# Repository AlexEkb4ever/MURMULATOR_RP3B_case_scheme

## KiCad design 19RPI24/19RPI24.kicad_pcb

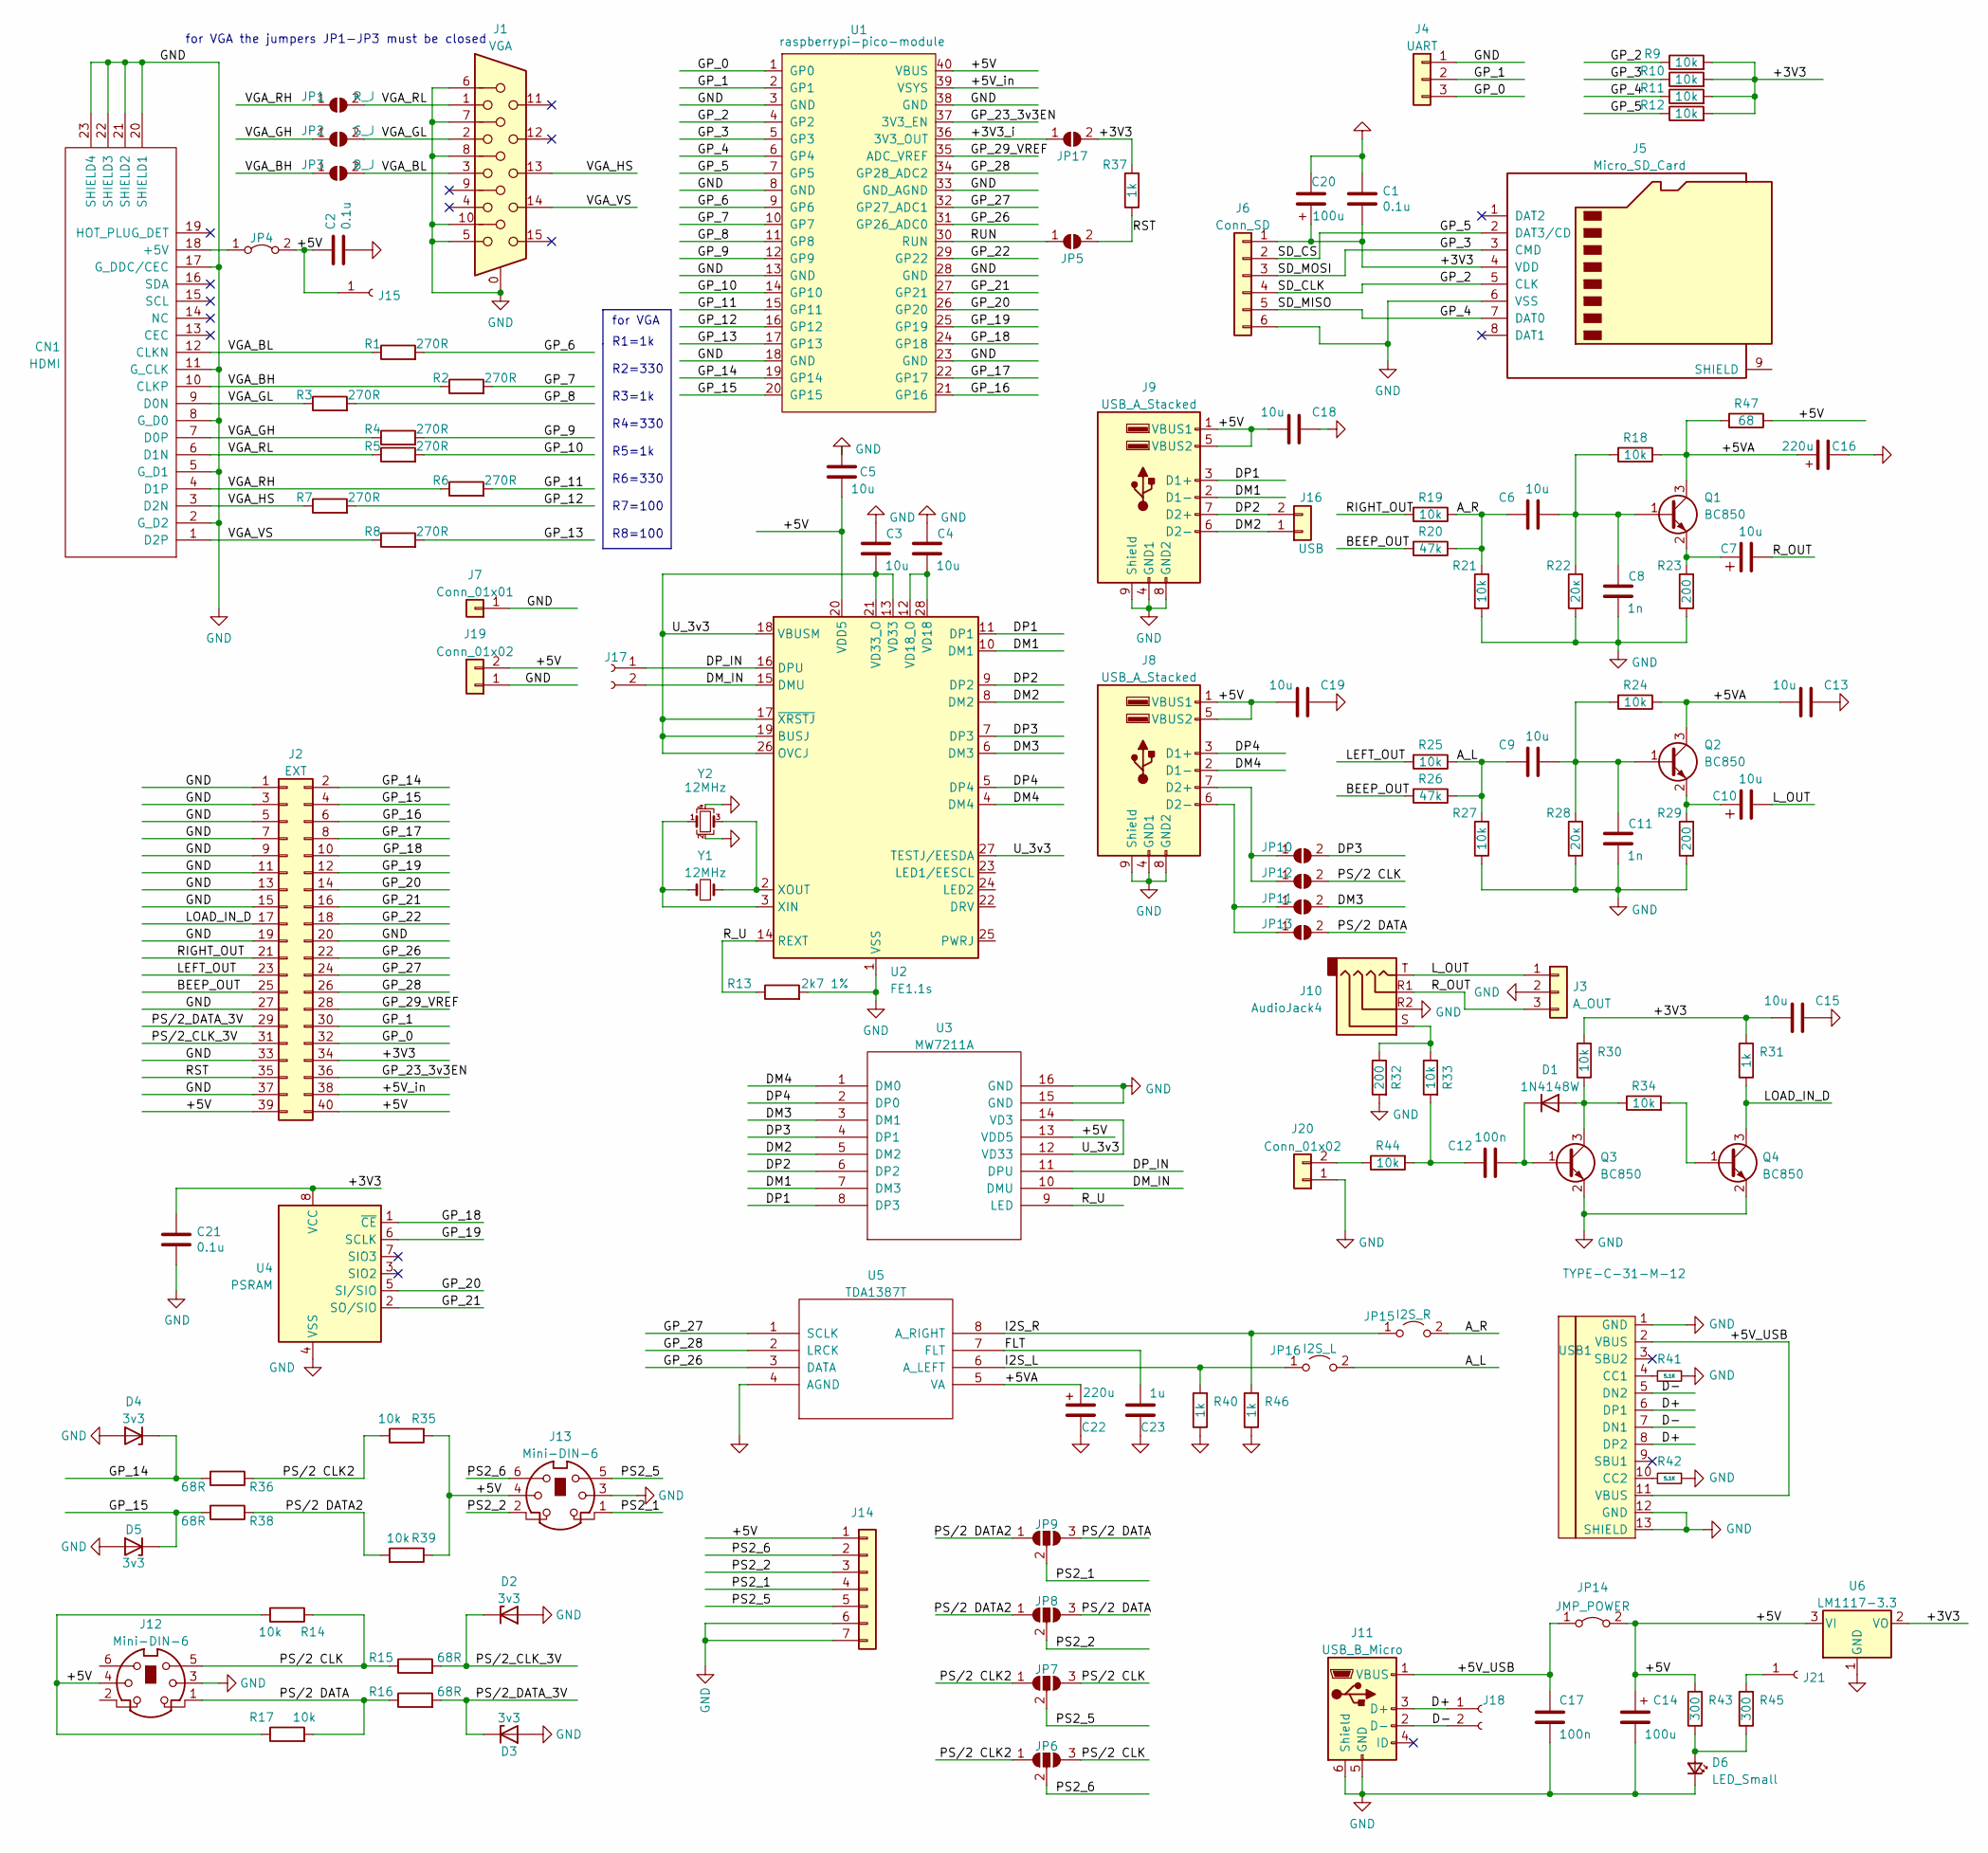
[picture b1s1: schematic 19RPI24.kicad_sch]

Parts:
C1, C21: 0.1u; C_0805_2012Metric_Pad1.18x1.45mm_HandSolder
C2: 0.1u; R_0805_PLUS
C3, C4, C5, C6, C9, C13, C15, C18, C19: 10u; C_0805_2012Metric_Pad1.18x1.45mm_HandSolder
C7, C10: 10u; c_comb_pol
C8, C11: 1n; C_0805_2012Metric_Pad1.18x1.45mm_HandSolder
C12, C17: 100n; C_0805_2012Metric_Pad1.18x1.45mm_HandSolder
C14, C20: 100u; c_comb_pol
C16: 220u; CP_EIA-3528-21_Kemet-B_Pad1.50x2.35mm_HandSolder
C22: 220u; CP_EIA-6032-28_Kemet-C
C23: 1u; C_0805_2012Metric_Pad1.18x1.45mm_HandSolder
CN1: HDMI
D1: 1N4148W; D_SOD-123
D2, D3, D4, D5: 3v3; D_0805_PLUS
D6: LED_Small; LED_1206_3216Metric_Pad1.42x1.75mm_HandSolder
J1: VGA; DSUB-15-HD_Female_Horizontal_P2.29x1.98mm_EdgePinOffset3.03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
J2: EXT; PinHeader_2x20_P2.54mm_Vertical
J3: A_OUT; PinHeader_1x03_P2.54mm_Vertical
J4: UART; PinHeader_1x03_P2.54mm_Vertical
J5: Micro_SD_Card; GCT-MEM2055-00-190-01-A
J6: Conn_SD; PinSocket_1x06_P2.54mm_Vertical
J7: Conn_01x01; PinHeader_1x01_P2.54mm_Vertical
J8, J9: USB_A_Stacked; USB_A_Wuerth_61400826021_Horizontal_Stacked
J10: AudioJack4; Jack_3.5mm_PJ320D_Horizontal
J11: USB_B_Micro; USB_Micro-B_Amphenol
J12, J13: Mini-DIN-6; Connector_Mini-DIN_Female_6Pin
J14: Conn_01x07; PinHeader_1x07_P2.54mm_Vertical
J15: Conn_01x01_Female; conn_1
J16: USB; PinHeader_1x02_P2.54mm_Vertical
J17, J18: Conn_01x02_Female; conn 2
J19, J20: Conn_01x02; PinHeader_1x02_P2.54mm_Vertical
J21: Conn_01x01_Female; Pin_D0.7mm_L6.5mm_W1.8mm_FlatFork
JP1, JP5, JP17: R_J; SolderJumper-2_P1.3mm_Open_RoundedPad1.0x1.5mm
JP2: G_J; SolderJumper-2_P1.3mm_Open_RoundedPad1.0x1.5mm
JP3: B_J; SolderJumper-2_P1.3mm_Open_RoundedPad1.0x1.5mm
JP4: Jumper_2_Bridged; SolderJumper-2_P1.3mm_Bridged_RoundedPad1.0x1.5mm
JP6, JP7, JP8, JP9: SolderJumper_3_Open; SolderJumper-3_P1.3mm_Open_RoundedPad1.0x1.5mm
JP10, JP11, JP12, JP13: J; SolderJumper-2_P1.3mm_Open_RoundedPad1.0x1.5mm
JP14: JMP_POWER; SolderJumper-2_P1.3mm_Bridged_RoundedPad1.0x1.5mm
JP15: I2S_R; PinHeader_1x02_P2.54mm_Vertical
JP16: I2S_L; PinHeader_1x02_P2.54mm_Vertical
Q1, Q2, Q3, Q4: BC850; SOT-23
R1, R2, R3, R4, R5, R6, R7, R8: 270R; R_0805_PLUS
R9, R10, R11, R12, R14, R17, R18, R19, R21, R24, R25, R27, R30, R33, R34, R35, R39, R44: 10k; R_0805_2012Metric_Pad1.20x1.40mm_HandSolder
R13: 2k7 1%; R_0805_2012Metric_Pad1.20x1.40mm_HandSolder
R15, R16, R36, R38: 68R; R_0805_2012Metric_Pad1.20x1.40mm_HandSolder
R20, R26: 47k; R_0805_2012Metric_Pad1.20x1.40mm_HandSolder
R22, R28: 20к; R_0805_2012Metric_Pad1.20x1.40mm_HandSolder
R23, R29, R32: 200; R_0805_2012Metric_Pad1.20x1.40mm_HandSolder
R31, R37, R40, R46: 1k; R_0805_2012Metric_Pad1.20x1.40mm_HandSolder
R41, R42: 5.1K; R_0805_2012Metric_Pad1.20x1.40mm_HandSolder
R43, R45: 300; R_0805_2012Metric_Pad1.20x1.40mm_HandSolder
R47: 68; R_0805_2012Metric_Pad1.20x1.40mm_HandSolder
U1: raspberrypi-pico-module; Raspberry_Pi_Pico_SMT_THT_MOD_3
U2: FE1.1s; SSOP-28_3.9x9.9mm_P0.635mm
U3: MW7211A; SO-16_5.3x10.2mm_P1.27mm
U4: PSRAM; SO-8_5.3x6.2mm_P1.27mm
U5: TDA1387T; SO-8_5.3x6.2mm_P1.27mm
U6: LM1117-3.3; SOT-223-3_TabPin2
USB1: TYPE-C-31-M-12; USB-TYPE-C-31-M-12_lib2; LCSC C165948
Y1: 12MHz; Crystal_HC49-4H_Vertical
Y2: 12MHz; Crystal_SMD_0603-4Pin_6.0x3.5mm

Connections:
/+3V3: C1.2, C15.2, C20.1, C21.1, J2.34, J5.4 (VDD), J6.1, JP17.2 (B), R9.2, R10.2, R11.2, R12.2, R30.2, R31.2, R37.2, U4.8 (VCC), U6.2 (VO); also elsewhere on the board
/+3V3_i: JP17.1 (A), U1.36 (3V3_OUT)
/+5V: C2.1, C5.2, C14.1, C18.2, C19.2, J2.39, J2.40, J8.1 (VBUS1), J8.5 (VBUS2), J9.1 (VBUS1), J9.5 (VBUS2), J12.4, J13.4, J14.1, J15.1, J19.2, JP4.2 (B), JP14.2 (B), R14.2, R17.1, R35.2, R39.1, R43.2, R47.1, U1.40 (VBUS), U2.20 (VDD5), U3.13 (VDD5), U6.3 (VI)
/+5VA: C13.2, C16.1, C22.1, Q1.3 (C), Q2.3 (C), R18.1, R24.1, R47.2, U5.5 (VA)
/+5V_USB: C17.1, J11.1 (VBUS), JP14.1 (A), USB1.2 (VBUS), USB1.11 (VBUS)
/+5V_in: J2.38, U1.39 (VSYS)
/A_L: C9.1, JP16.2 (B), R25.1, R26.1, R27.2
/A_R: C6.1, JP15.2 (B), R19.1, R20.1, R21.2
/BEEP_OUT: J2.25, R20.2, R26.2
/D+: J11.3 (D+), J18.1, USB1.6 (DP1), USB1.8 (DP2)
/D-: J11.2 (D-), J18.2, USB1.5 (DN2), USB1.7 (DN1)
/DM1: J9.2 (D1-), U2.10 (DM1), U3.7 (DM3)
/DM2: J9.6 (D2-), J16.1, U2.8 (DM2), U3.5 (DM2)
/DM3: JP11.2 (B), U2.6 (DM3), U3.3 (DM1)
/DM4: J8.2 (D1-), U2.4 (DM4), U3.1 (DM0)
/DM_IN: J17.2, U2.15 (DMU), U3.10 (DMU)
/DP1: J9.3 (D1+), U2.11 (DP1), U3.8 (DP3)
/DP2: J9.7 (D2+), J16.2, U2.9 (DP2), U3.6 (DP2)
/DP3: JP10.2 (B), U2.7 (DP3), U3.4 (DP1)
/DP4: J8.3 (D1+), U2.5 (DP4), U3.2 (DP0)
/DP_IN: J17.1, U2.16 (DPU), U3.11 (DPU)
/FLT: C23.2, U5.7 (FLT)
/GP_0: J2.32, J4.3, U1.1 (GP0)
/GP_1: J2.30, J4.2, U1.2 (GP1)
/GP_2: J5.5 (CLK), J6.4, R9.1, U1.4 (GP2)
/GP_3: J5.3 (CMD), J6.3, R10.1, U1.5 (GP3)
/GP_4: J5.7 (DAT0), J6.5, R11.1, U1.6 (GP4)
/GP_5: J5.2 (DAT3/CD), J6.2, R12.1, U1.7 (GP5)
/GP_6: R1.2, U1.9 (GP6)
/GP_7: R2.2, U1.10 (GP7)
/GP_8: R3.2, U1.11 (GP8)
/GP_9: R4.2, U1.12 (GP9)
/GP_10: R5.2, U1.14 (GP10)
/GP_11: R6.2, U1.15 (GP11)
/GP_12: R7.2, U1.16 (GP12)
/GP_13: R8.2, U1.17 (GP13)
/GP_14: D4.1 (K), J2.2, R36.2, U1.19 (GP14)
/GP_15: D5.1 (K), J2.4, R38.2, U1.20 (GP15)
/GP_16: J2.6, U1.21 (GP16)
/GP_17: J2.8, U1.22 (GP17)
/GP_18: J2.10, U1.24 (GP18), U4.1 (~CE)
/GP_19: J2.12, U1.25 (GP19), U4.6 (SCLK)
/GP_20: J2.14, U1.26 (GP20), U4.5 (SI/SIO)
/GP_21: J2.16, U1.27 (GP21), U4.2 (SO/SIO)
/GP_22: J2.18, U1.29 (GP22)
/GP_23_3v3EN: J2.36, U1.37 (3V3_EN)
/GP_26: J2.22, U1.31 (GP26_ADC0), U5.3 (DATA)
/GP_27: J2.24, U1.32 (GP27_ADC1), U5.1 (SCLK)
/GP_28: J2.26, U1.34 (GP28_ADC2), U5.2 (LRCK)
/GP_29_VREF: J2.28, U1.35 (ADC_VREF)
/I2S_L: JP16.1 (A), R40.2, U5.6 (A_LEFT)
/I2S_R: JP15.1 (A), R46.2, U5.8 (A_RIGHT)
/LEFT_OUT: J2.23, R25.2
/LOAD_IN_D: J2.17, Q4.3 (C), R31.1
/L_OUT: C10.2, J3.1, J10.T
/PS2_1: J13.1, J14.4, JP9.2 (C)
/PS2_2: J13.2, J14.3, JP8.2 (C)
/PS2_5: J13.5, J14.5, JP7.2 (C)
/PS2_6: J13.6, J14.2, JP6.2 (C)
/PS/2 CLK: J12.5, JP6.3 (B), JP7.3 (B), JP12.2 (B), R14.1, R15.1
/PS/2 CLK2: JP6.1 (A), JP7.1 (A), R35.1, R36.1
/PS/2 DATA: J12.1, JP8.3 (B), JP9.3 (B), JP13.2 (B), R16.1, R17.2
/PS/2 DATA2: JP8.1 (A), JP9.1 (A), R38.1, R39.2
/PS/2_CLK_3V: D2.1 (K), J2.31, R15.2
/PS/2_DATA_3V: D3.1 (K), J2.29, R16.2
/RIGHT_OUT: J2.21, R19.2
/RST: J2.35, JP5.2 (B), R37.1
/RUN: JP5.1 (A), U1.30 (RUN)
/R_OUT: C7.2, J3.3, J10.R1
/R_U: R13.1, U2.14 (REXT), U3.9 (LED)
/U_3v3: C3.2, U2.13 (VD33), U2.17 (~XRSTJ), U2.18 (VBUSM), U2.19 (BUSJ), U2.21 (VD33_O), U2.26 (OVCJ), U2.27 (TESTJ/EESDA), U3.12 (VD33), U3.14 (VD3)
/VGA_BH: CN1.10 (CLKP), JP3.1 (A), R2.1
/VGA_BL: CN1.12 (CLKN), J1.3, JP3.2 (B), R1.1
/VGA_GH: CN1.7 (D0P), JP2.1 (A), R4.1
/VGA_GL: CN1.9 (D0N), J1.2, JP2.2 (B), R3.1
/VGA_HS: CN1.3 (D2N), J1.13, R7.1
/VGA_RH: CN1.4 (D1P), JP1.1 (A), R6.1
/VGA_RL: CN1.6 (D1N), J1.1, JP1.2 (B), R5.1
/VGA_VS: CN1.1 (D2P), J1.14, R8.1
GND: C1.1, C2.2, C3.1, C4.1, C5.1, C8.2, C11.2, C13.1, C14.2, C15.1, C16.2, C17.2, C18.1, C19.1, C20.2, C21.2, C22.2, C23.1, CN1.2 (G_D2), CN1.5 (G_D1), CN1.8 (G_D0), CN1.11 (G_CLK), CN1.17 (G_DDC/CEC), CN1.20 (SHIELD1), CN1.21 (SHIELD2), CN1.22 (SHIELD3), CN1.23 (SHIELD4), D2.2 (A), D3.2 (A), D4.2 (A), D5.2 (A), D6.1 (K), J1.0, J1.5, J1.6, J1.7, J1.8, J1.10, J2.1, J2.3, J2.5, J2.7, J2.9, J2.11, J2.13, J2.15, J2.19, J2.20, J2.27, J2.33, J2.37, J3.2, J4.1, J5.6 (VSS), J6.6, J7.1, J8.4 (GND1), J8.8 (GND2), J8.9 (Shield), J9.4 (GND1), J9.8 (GND2), J9.9 (Shield), J10.R2, J11.5 (GND), J11.6 (Shield), J12.3, J13.3, J14.6, J14.7, J19.1, J20.1, Q3.2 (E), Q4.2 (E), R13.2, R21.1, R22.1, R23.1, R27.1, R28.1, R29.1, R32.2, R40.1, R41.1, R42.1, R46.1, U1.3 (GND), U1.8 (GND), U1.13 (GND), U1.18 (GND), U1.23 (GND), U1.28 (GND), U1.33 (GND_AGND), U1.38 (GND), U2.1 (VSS), U3.15 (GND), U3.16 (GND), U4.4 (VSS), U5.4 (AGND), U6.1 (GND), USB1.1 (GND), USB1.12 (GND), USB1.13 (SHIELD), Y2.2, Y2.4; also elsewhere on the board
unnamed: C4.2, U2.12 (VD18_O), U2.28 (VD18)
unnamed: C6.2, C8.1, Q1.1 (B), R18.2, R22.2
unnamed: C7.1, Q1.2 (E), R23.2
unnamed: C10.1, Q2.2 (E), R29.2
unnamed: C9.2, C11.1, Q2.1 (B), R24.2, R28.2
unnamed: C12.1, R33.2, R44.2
unnamed: C12.2, D1.1 (K), Q3.1 (B)
unnamed: CN1.18 (+5V), JP4.1 (A)
unnamed: D1.2 (A), Q3.3 (C), R30.1, R34.1
unnamed: D6.2 (A), R43.1, R45.1
unnamed: J8.6 (D2-), JP11.1 (A), JP13.1 (A)
unnamed: J8.7 (D2+), JP10.1 (A), JP12.1 (A)
unnamed: J10.S, R32.1, R33.1
unnamed: J20.2, R44.1
unnamed: J21.1, R45.2
unnamed: Q4.1 (B), R34.2
unnamed: R41.2, USB1.4 (CC1)
unnamed: R42.2, USB1.10 (CC2)
unnamed: U2.2 (XOUT), Y1.2, Y2.3
unnamed: U2.3 (XIN), Y1.1, Y2.1

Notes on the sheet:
for VGA
for VGA the jumpers JP1-JP3 must be closed
R1=1k R2=330 R3=1k R4=330 R5=1k R6=330 R7=100 R8=100

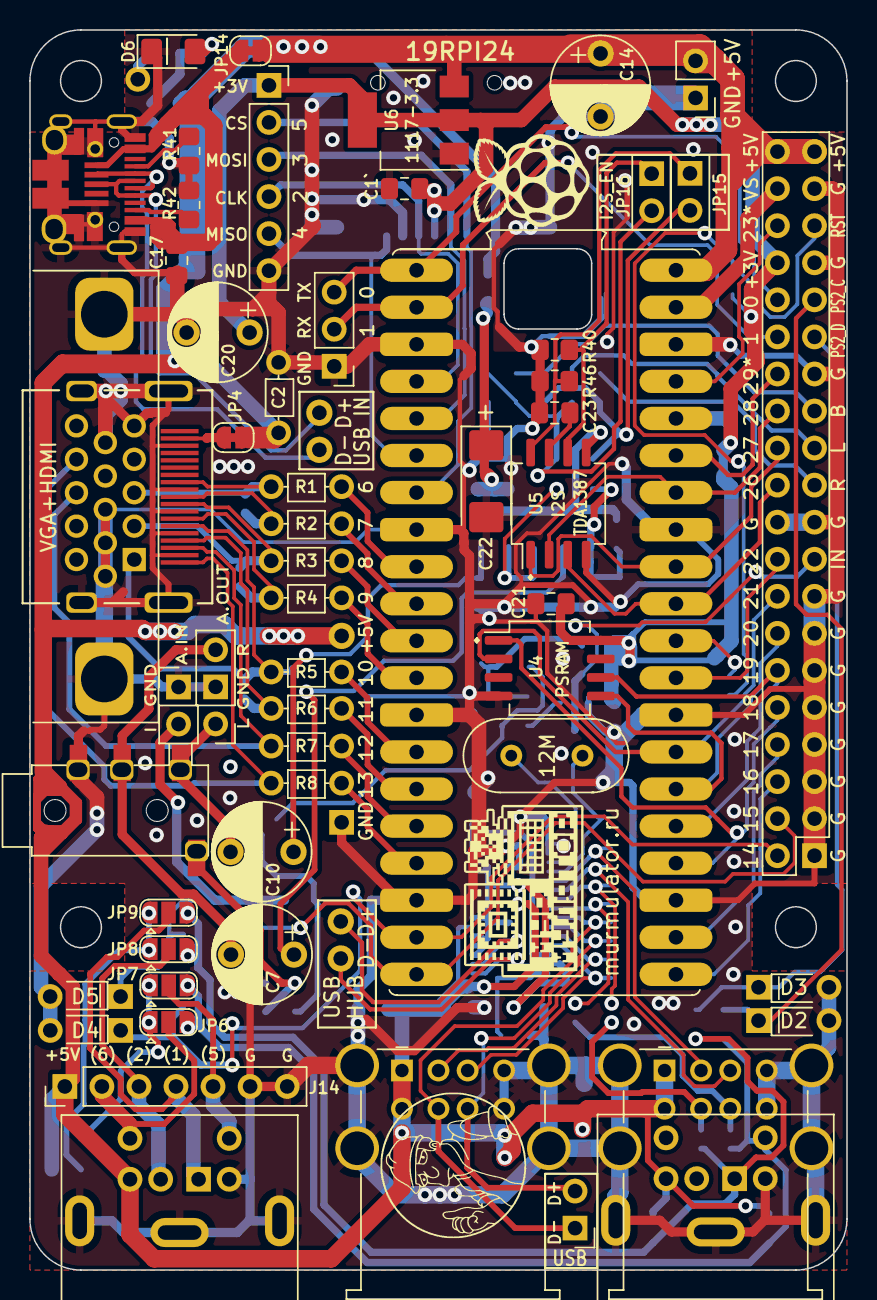
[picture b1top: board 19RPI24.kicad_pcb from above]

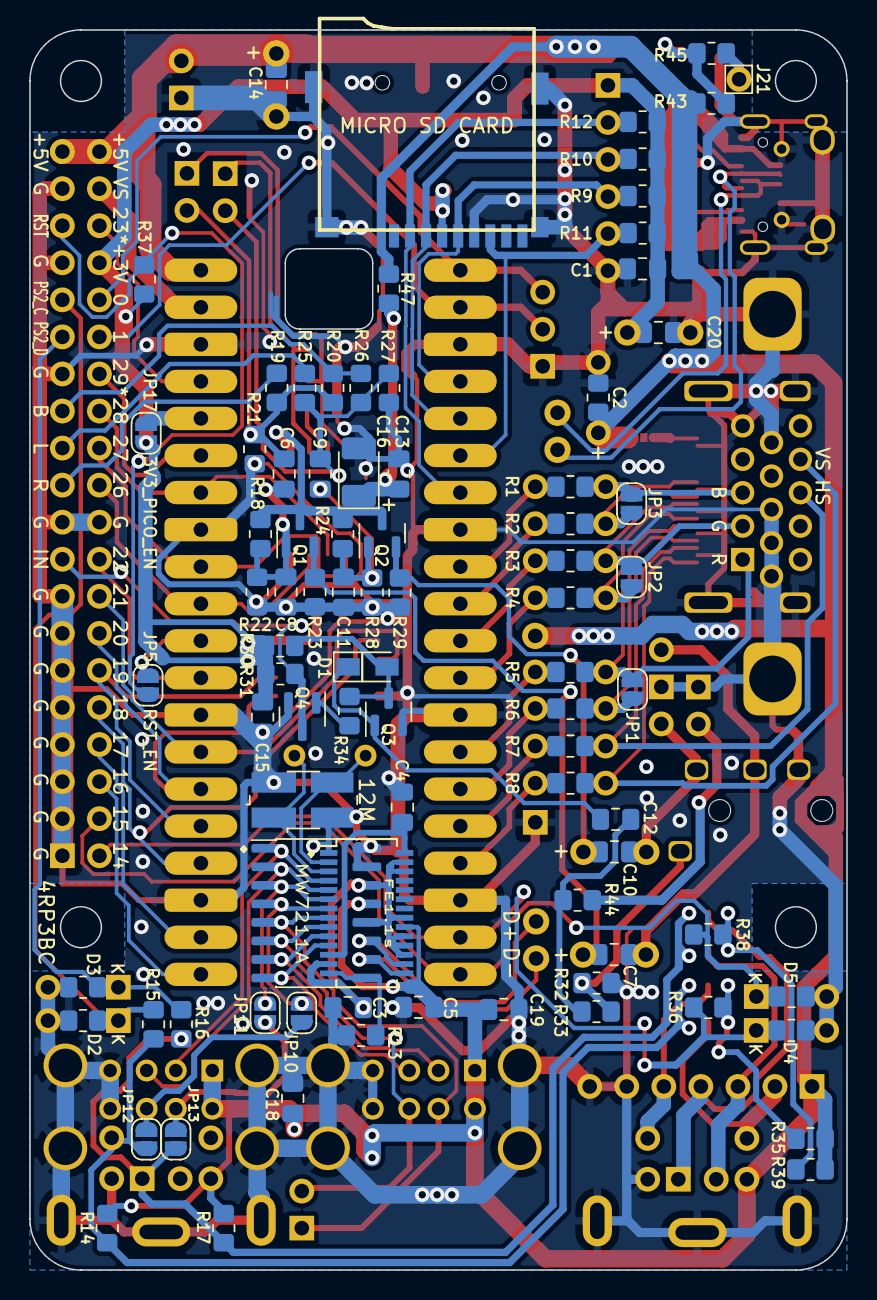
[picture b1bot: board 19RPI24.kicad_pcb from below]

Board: 2 copper layers, 56.0 x 85.0 mm, 129 parts (85 on the bottom side), 100 nets.

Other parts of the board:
C1`: 0.1u; C_0805_2012Metric_Pad1.18x1.45mm_HandSolder

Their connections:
/+3V3: C1`.2; also elsewhere on the board
GND: C1`.1; also elsewhere on the board

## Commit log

2023-08-15 create
2023-08-15 .
    Power Led
    USB IN d+ d- position
2023-08-15 labels
2023-08-18 +jumpers
    USB PS/2 jumpers
2024-01-02 usb comb
2024-05-04 16RP!24 create
2024-05-08 add 1117
